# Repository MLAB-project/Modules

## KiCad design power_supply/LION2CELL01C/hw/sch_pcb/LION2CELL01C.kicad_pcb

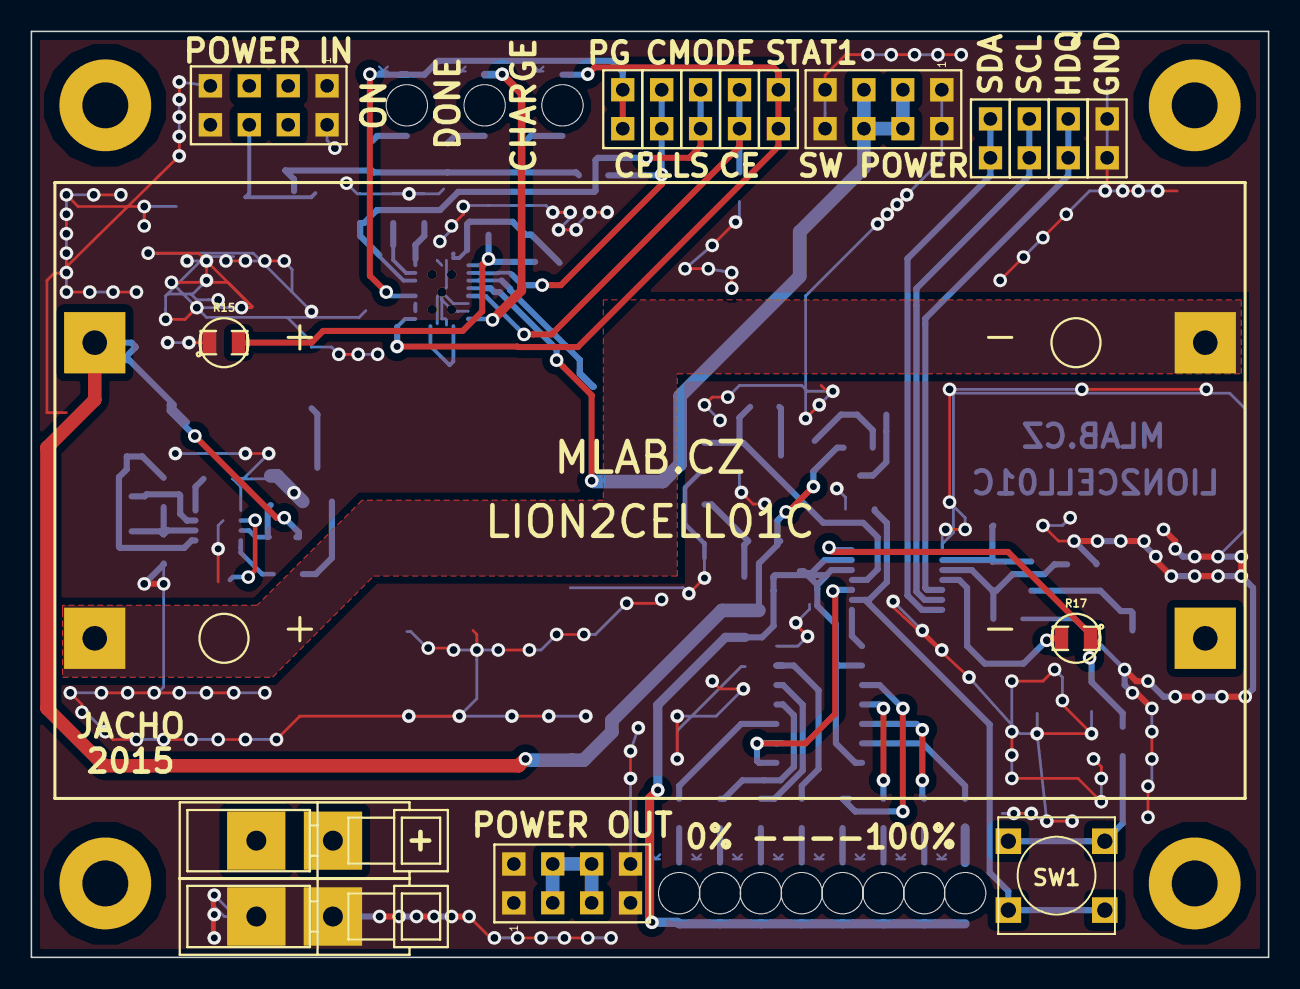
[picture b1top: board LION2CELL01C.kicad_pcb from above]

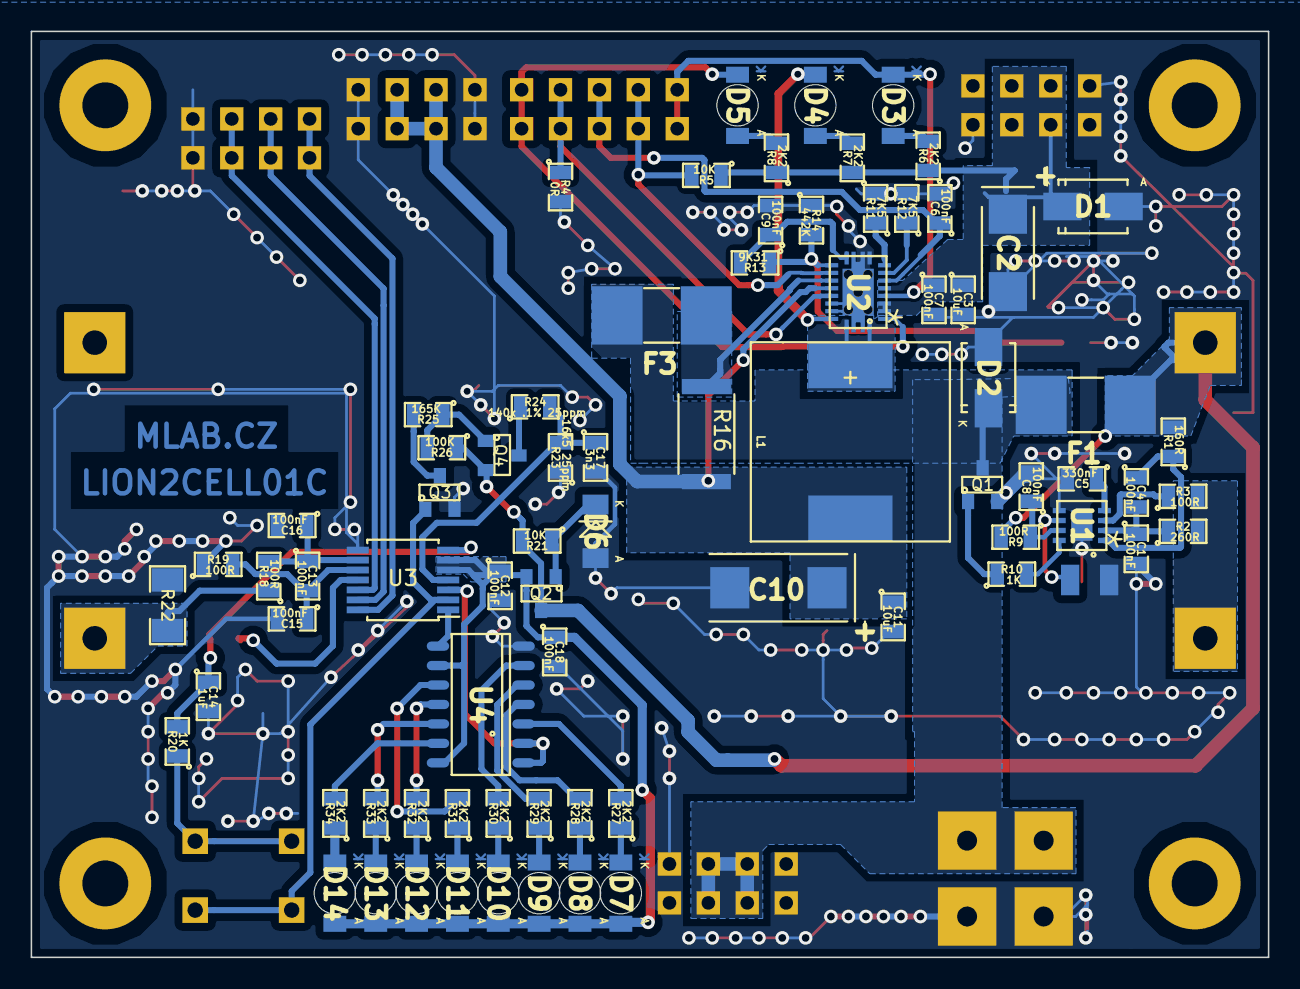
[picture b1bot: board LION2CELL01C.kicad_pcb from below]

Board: 2 copper layers, 80.8 x 60.5 mm, 98 parts (76 on the bottom side), 63 nets.

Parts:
BT1: 2x18650_LION-RESCUE-LION2CELL01C; 2LION
C1, C4, C6, C7, C8, C9, C12, C13, C15, C16, C18: 100nF; SMD-0805
C2: 47uF; TantalC_SizeC_Reflow
C3, C11: 10uF; SMD-0805
C5: 330nF; SMD-0805
C10: 100uF; TantalC_SizeD_Reflow
C14: 1uF; SMD-0805
C17: 3n3; SMD-0805
D1, D2: M4; SMA_Standard
D3, D4, D5: LED; LED_1206
D6: BZV55C-5,6V; MiniMELF_Standard
D7, D8, D9, D10, D11, D12, D13, D14: ORAGE; LED_1206
F1: 5A; Drzak_2410
F3: 2A; Drzak_2410
J1, J7, J13: JUMP_4X2; Straight_2x04
J2, J3, J4, J5, J6, J10, J11, J12, J14: JUMP_2x1; Straight_1x02
J8, J9: CONN1_1; WAGO256
J15: CONN_2; SMD_1_2x2
L1: DE1205-10
P1, P2, P3, P4: _; MountingHole_3mm
Q1: IRLML6244; SOT-23
Q2, Q3: MMBF170LT1G; SOT-23
Q4: BSS83P; SOT-23
R1: 160R; SMD-0805
R2: 260R; SMD-0805
R3, R9, R18, R19: 100R; SMD-0805
R4: 0R; SMD-0805
R5, R21: 10K; SMD-0805
R6, R7, R8, R27, R28, R29, R30, R31, R32, R33, R34: 2K2; SMD-0805
R10, R20: 1K; SMD-0805
R11, R12: 7K5; SMD-0805
R13: 9K31; SMD-0805
R14: 442K; SMD-0805
R15: NCP21XV103J03RA; SMD-0805
R16: 0R1; R_2512
R17: 10K NTC; SMD-0805
R22: 0R01 75PPM; SMD-1206
R23: 16k5 25ppm; SMD-0805
R24: 140k .1% 25ppm; SMD-0805
R25: 165K; SMD-0805
R26: 100K; SMD-0805
SW1: SW_PUSH; SW_PUSH_SMALL
U1: BQ29209; VSON-8
U2: BQ24103; VQFN-20
U3: BQ34Z100; TSSOP-14_4.4x5mm_Pitch0.65mm
U4: SN74HC164D; SO-14

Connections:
/BAT+: BT1.1, F1.1, Q2.D, Q4.S, R1.2, R9.2, R21.2, R26.1
/BAT-MIDPOINT: BT1.2, BT1.3, R2.2, R3.2
/BATTERY+: D2.2, F1.2, F3.2, J7.3, J7.4, J7.5, J7.6, J8.1, Q1.D
/BATTERY-: BT1.4, R18.1, R22.1
/CE: J5.1, J5.2, R4.1, U2.16
/CELLS: J6.1, J6.2, R5.2, U2.13
/CMODE: C6.1, J4.1, J4.2, U2.7
/HDQ: J12.1, J12.2, U3.12
/P1: U3.3, U4.1, U4.2
/P2: U3.1, U4.8
/PG: D3.2, J3.1, J3.2, U2.5
/REGIN: C12.1, C18.1, D7.1, D8.1, D9.1, D10.1, D11.1, D12.1, D13.1, D14.1, Q2.S, U3.5, U3.6, U4.9, U4.14
/SCL: J11.1, J11.2, U3.13
/SDA: J10.1, J10.2, U3.14
/STAT1: D5.2, J2.1, J2.2, U2.2
GND: C1.2, C2.2, C3.2, C5.2, C6.2, C7.2, C8.2, C9.2, C10.2, C11.2, C12.2, C14.2, C15.2, C16.2, C17.2, C18.2, D1.1, D2.1, D6.1, J1.1, J1.2, J1.7, J1.8, J7.1, J7.2, J7.7, J7.8, J9.1, J13.1, J13.2, J13.7, J13.8, J14.1, J14.2, J15.2, Q1.S, Q3.S, R4.2, R11.2, R12.2, R14.1, R15.1, R19.1, R22.2, R23.1, U1.5, U1.9, U2.10, U2.17, U2.18, U2.21, U3.8, U4.7
unnamed: C1.1, C4.2, R2.1, U1.2
unnamed: C2.1, C3.1, C7.1, D1.2, J1.3, J1.4, J1.5, J1.6, R5.1, R6.1, R7.1, R8.1, U2.3, U2.4, U2.6
unnamed: C4.1, R1.1, U1.1
unnamed: C5.1, U1.4
unnamed: C8.1, R9.1, U1.7
unnamed: C9.1, R13.2
unnamed: C10.1, C11.1, J13.3, J13.4, J13.5, J13.6, L1.2, R16.2, U2.15
unnamed: C13.1, C16.1, R18.2, U3.9
unnamed: C13.2, C15.1, R19.2, U3.10
unnamed: C14.1, R17.1, R20.2, U3.7
unnamed: C17.1, R23.2, R24.2
unnamed: D3.1, R6.2
unnamed: D4.1, R7.2
unnamed: D4.2, U2.19
unnamed: D5.1, R8.2
unnamed: D6.2, Q2.G, R21.1
unnamed: D7.2, R27.1
unnamed: D8.2, R28.1
unnamed: D9.2, R29.1
unnamed: D10.2, R30.1
unnamed: D11.2, R31.1
unnamed: D12.2, R32.1
unnamed: D13.2, R33.1
unnamed: D14.2, R34.1
unnamed: F3.1, R16.1, U2.14
unnamed: J15.1, U1.6
unnamed: L1.1, U2.1, U2.20
unnamed: Q1.G, R10.1
unnamed: Q3.D, R25.2
unnamed: Q3.G, SW1.2, U3.2
unnamed: Q4.D, R24.1
unnamed: Q4.G, R25.1, R26.2
unnamed: R3.1, U1.3
unnamed: R10.2, U1.8
unnamed: R11.1, U2.9
unnamed: R12.1, U2.8
unnamed: R13.1, R14.2, R15.2, U2.12
unnamed: R17.2, U3.11
unnamed: R20.1, SW1.1
unnamed: R27.2, U4.3
unnamed: R28.2, U4.4
unnamed: R29.2, U4.5
unnamed: R30.2, U4.6
unnamed: R31.2, U4.10
unnamed: R32.2, U4.11
unnamed: R33.2, U4.12
unnamed: R34.2, U4.13

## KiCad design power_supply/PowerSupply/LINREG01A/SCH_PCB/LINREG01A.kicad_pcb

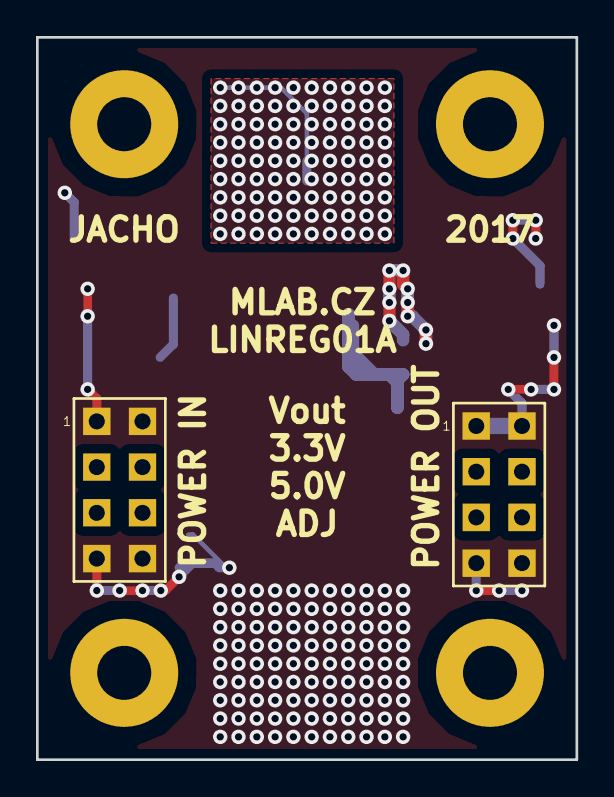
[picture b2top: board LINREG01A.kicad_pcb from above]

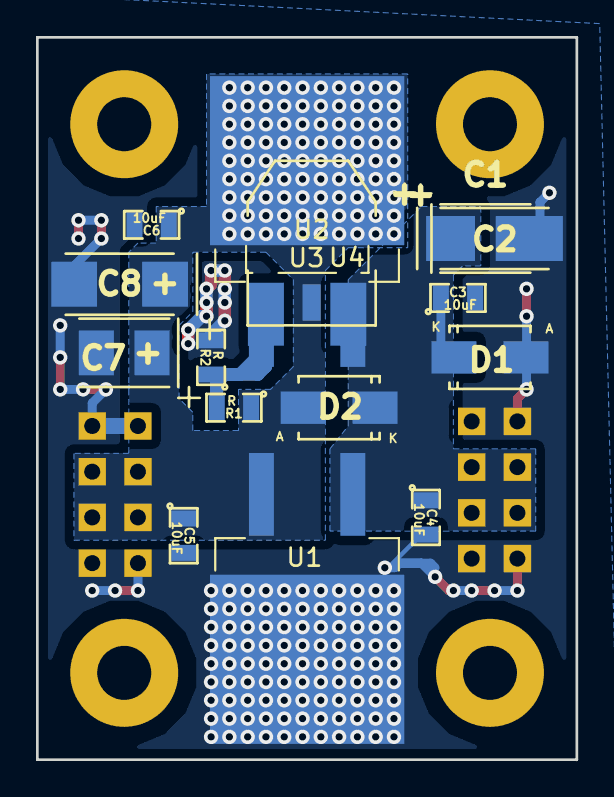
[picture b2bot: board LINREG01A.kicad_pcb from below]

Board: 2 copper layers, 30.0 x 40.1 mm, 22 parts (16 on the bottom side), 4 nets.

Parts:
C1, C7: 10uF; TantalC_SizeB_Reflow
C2, C8: 47uF; TantalC_SizeC_Reflow
C3, C4, C5, C6: 10uF; SMD-0805
D1, D2: M4; Diode-SMA_Standard
J1, J2: HEADER_2x04_PARALLEL; Straight_2x04
M1, M2, M3, M4: HOLE; MountingHole_3mm
R1, R2: R; SMD-0805
U1: L78_DPAK_D2PAK; D2PAK-TO-263-2Lead
U2: LM1117_ADJ_SOT; SOT-223
U3: LM317M_LM217_DPAK_D2PAK; D2PAK-TO-263-2Lead
U4: LM317M_LM217_DPAK_D2PAK; DPAK-TO-252-2Lead

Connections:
/ADJ: R1.2, R2.1, U2.1, U3.1, U4.1
/OUT: C5.1, C6.1, C7.1, C8.1, D2.2, J2.3, J2.4, J2.5, J2.6, R1.1, U1.3, U2.2, U2.4, U3.4, U4.4
GND: C1.2, C2.2, C3.2, C4.2, C5.2, C6.2, C7.2, C8.2, D1.2, J1.1, J1.2, J1.7, J1.8, J2.1, J2.2, J2.7, J2.8, R2.2, U1.4
VCC: C1.1, C2.1, C3.1, C4.1, D1.1, D2.1, J1.3, J1.4, J1.5, J1.6, U1.1, U2.3, U3.3, U4.3

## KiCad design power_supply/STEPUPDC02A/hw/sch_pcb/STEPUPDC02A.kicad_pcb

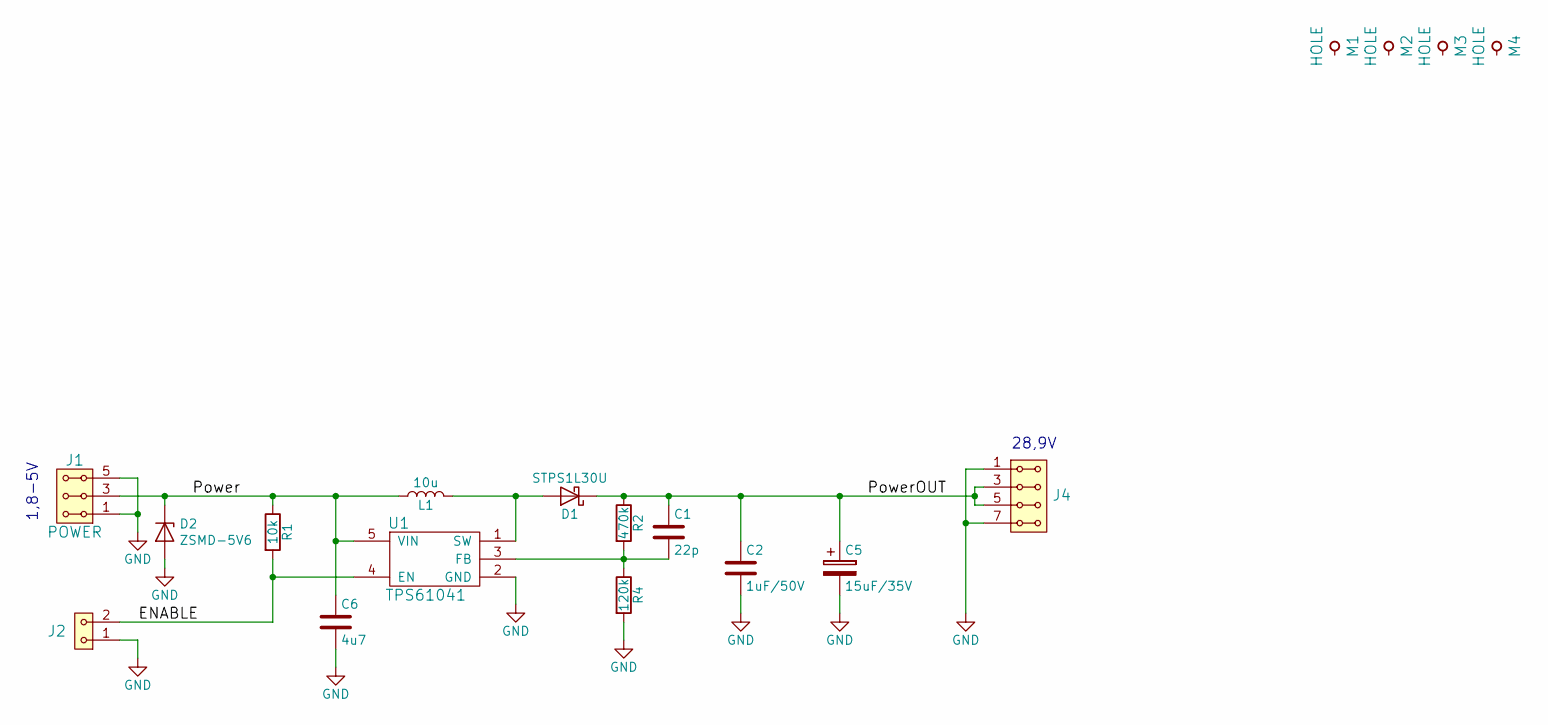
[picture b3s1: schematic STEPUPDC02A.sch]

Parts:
C1: 22p; SMD-0805
C2: 1uF/50V; SMD-0805
C5: 15uF/35V; TantalC_SizeC_Reflow
C6: 4u7; SMD-0805
D1: STPS1L30U; D_SMB
D2: ZSMD-5V6; D_MiniMELF
J1: POWER; Straight_2x03
J2: HEADER_1x02; Straight_2x01
J4: HEADER_2x04_PARALLEL; Straight_2x04
L1: 10u; DJNR5040
M1, M2, M3, M4: HOLE; MountingHole_3mm
R1: 10k; SMD-0805
R2: 470k; SMD-0805
R4: 120k; SMD-0805
U1: TPS61041; SOT-23-5_HandSoldering

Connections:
/ENABLE: J2.2, R1.2, U1.4 (EN)
/Power: C6.1, D2.1 (K), J1.3, J1.4, L1.1, R1.1, U1.5 (VIN)
/PowerOUT: C1.1, C2.1, C5.1, D1.1 (K), J4.3, J4.4, J4.5, J4.6, R2.1
GND: C2.2, C5.2, C6.2, D2.2 (A), J1.1, J1.2, J1.5, J1.6, J2.1, J4.1, J4.2, J4.7, J4.8, R4.2, U1.2 (GND)
unnamed: C1.2, R2.2, R4.1, U1.3 (FB)
unnamed: D1.2 (A), L1.2, U1.1 (SW)

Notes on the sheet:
1,8-5V
28,9V

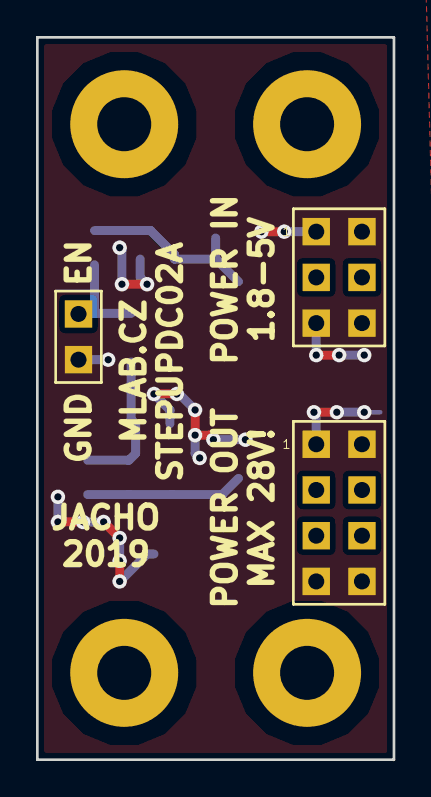
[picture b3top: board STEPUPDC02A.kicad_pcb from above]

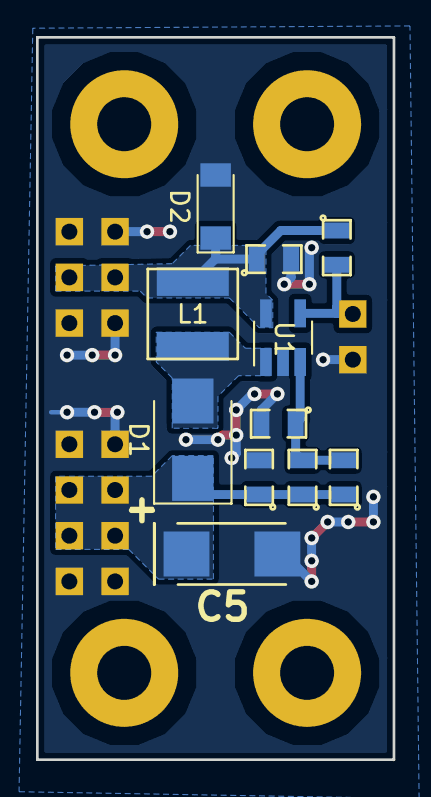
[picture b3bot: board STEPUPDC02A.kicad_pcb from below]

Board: 2 copper layers, 19.8 x 40.1 mm, 18 parts (11 on the bottom side), 6 nets.

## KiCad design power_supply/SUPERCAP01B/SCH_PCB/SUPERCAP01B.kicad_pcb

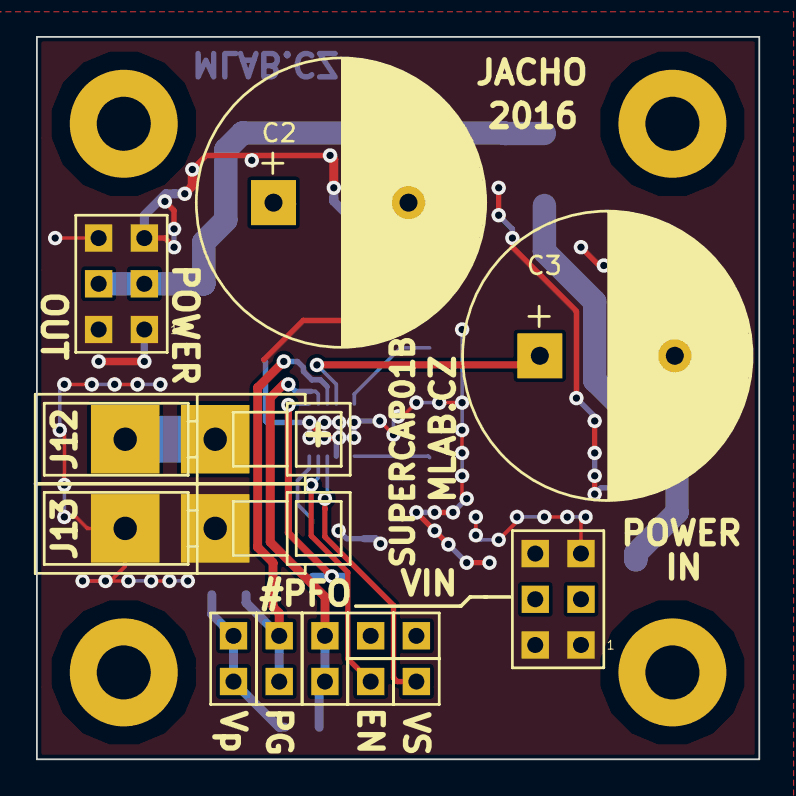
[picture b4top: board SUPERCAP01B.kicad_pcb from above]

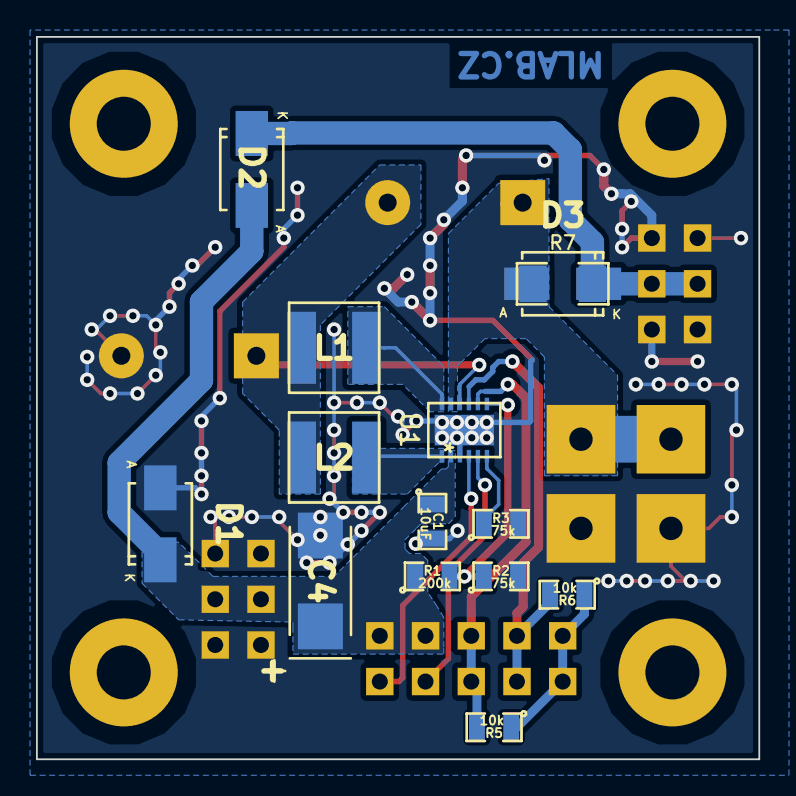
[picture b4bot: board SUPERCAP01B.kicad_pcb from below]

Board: 2 copper layers, 40.1 x 40.1 mm, 31 parts (14 on the bottom side), 14 nets.

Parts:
C1: 10uF; SMD-0805
C2, C3: 22F; C_Radial_D16_L25_P7.5
C4: 47uF; TantalC_SizeC_Reflow
D1: M4; SMA_Standard
D2, D3: 15MQ040N; Diode-SMA_Standard
J1, J11: JUMP_3X2; Straight_2x03
J5, J6, J7, J8: CONN1_1; Straight_1x01
J9, J10, J14: JUMP_2x1; Straight_2x01
J12, J13: CONN1_1; WAGO256
L1, L2: DJNR5040-3R3-S; DJNR5040
M1, M2, M3, M4: HOLE; MountingHole_3mm
R1: 200k; SMD-0805
R2, R3: 75k; SMD-0805
R5, R6: 10k; SMD-0805
R7: 0R; SMD-1206
U1: LTC3625; DFN-12-1EP_3x4mm_Pitch0.5mm

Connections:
/#PFO: J9.1, J9.2, R5.2, U1.8
/EN: J6.1, U1.5
/OUT: C2.1, D3.2, J12.1, R7.2, U1.11
/OUT2: D2.1, D3.1, J11.3, J11.4, R7.1
/PG: J10.1, J10.2, R6.2, U1.9
/VIN: C1.1, C4.1, D1.1, D2.2, J1.3, J1.4, J5.1, J7.1, R1.1, U1.2
/VSEL: J8.1, U1.4
/Vpull-up: J14.1, J14.2, R5.1, R6.1
GND: C1.2, C3.2, C4.2, D1.2, J1.1, J1.2, J1.5, J1.6, J11.1, J11.2, J11.5, J11.6, J13.1, R2.2, R3.2, U1.3, U1.13
unnamed: C2.2, C3.1, L1.2, L2.2, U1.10
unnamed: L1.1, U1.12
unnamed: L2.1, U1.1
unnamed: R1.2, R2.1, U1.7
unnamed: R3.1, U1.6

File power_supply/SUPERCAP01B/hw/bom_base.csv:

C;SMD-0805;10uF;['C1\r']
D_Schottky;Diode-SMA_Standard;15MQ040N;['D2\r', 'D3\r']
LTC3625;DFN-12-1EP_3x4mm_Pitch0.5mm;LTC3625;['U1\r']
DIODE;SMA_Standard;M4;['D1\r']
JUMP_2x1;Straight_2x01;JUMP_2x1;['J9\r', 'J10\r', 'J14\r']
CONN1_1;Straight_1x01;CONN1_1;['J7\r', 'J8\r', 'J6\r', 'J5\r']
CONN1_1;WAGO256;CONN1_1;['J12\r', 'J13\r']
R;SMD-0805;75k;['R2\r', 'R3\r']
R;SMD-0805;200k;['R1\r']
R;SMD-0805;10k;['R5\r', 'R6\r']
R;SMD-1206;0R;['R7\r']
INDUCTOR_SMALL;DJNR5040;DJNR5040-3R3-S;['L1\r', 'L2\r']
JUMP_3X2;Straight_2x03;JUMP_3X2;['J1\r', 'J11\r']
HOLE;MountingHole_3mm;HOLE;['M1\r', 'M3\r', 'M2\r', 'M4\r']
CP;TantalC_SizeC_Reflow;47uF;['C4\r']
CP;C_Radial_D16_L25_P7.5;22F;['C3\r', 'C2\r']

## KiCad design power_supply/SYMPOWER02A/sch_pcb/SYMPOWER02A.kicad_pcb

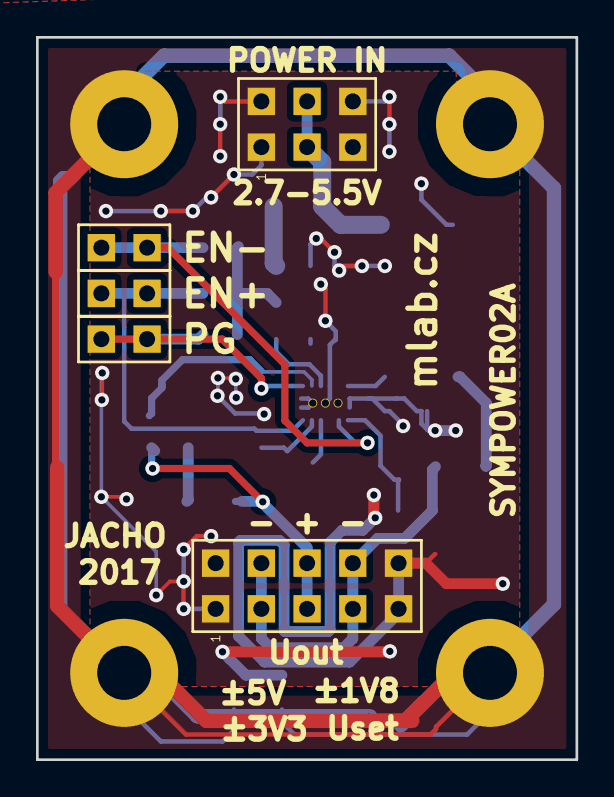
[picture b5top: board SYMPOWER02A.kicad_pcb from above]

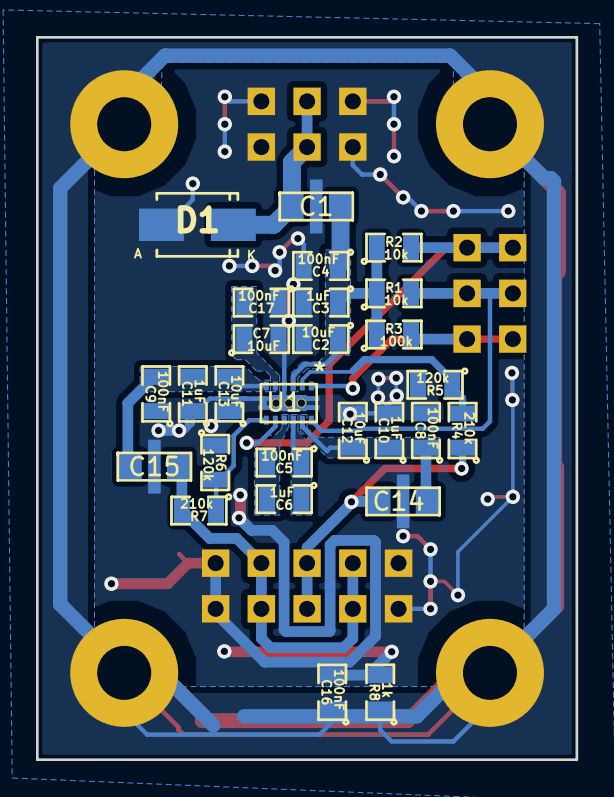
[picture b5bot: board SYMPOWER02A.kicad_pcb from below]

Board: 2 copper layers, 30.0 x 40.1 mm, 36 parts (27 on the bottom side), 16 nets.

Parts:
C1, C14, C15: NFM21PC105; FIR1
C2, C7, C12, C13: 10uF; SMD-0805
C3, C6, C10, C11: 1uF; SMD-0805
C4, C5, C8, C9, C16, C17: 100nF; SMD-0805
D1: M4; SMA_Standard
J1: HEADER_2x03_PARALLEL; Straight_2x03
J2, J3, J4: HEADER_2x01_PARALLEL; Straight_2x01
J5: HEADER_2x05_PARALLEL; Straight_2x05
M1, M2, M3, M4: HOLE; MountingHole_3mm
R1, R2: 10k; SMD-0805
R3: 100k; SMD-0805
R4, R7: 210k; SMD-0805
R5, R6: 120k; SMD-0805
R8: 1k; SMD-0805
U1: LM27762; WSON-12

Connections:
/C1+: C5.1, C6.1, U1.10
/C1-: C5.2, C6.2, U1.9
/CP: C7.1, C17.2, U1.5
/EN+: J2.1, J2.2, R1.2, U1.12
/EN-: J3.1, J3.2, R2.2, U1.8
/FB+: R4.2, R5.1, U1.2
/FB-: R6.2, R7.1, U1.7
/PGOOD: J4.1, J4.2, R3.2, U1.1
/Vout+: C14.3, J5.5, J5.6, R4.1
/Vout-: C15.3, J5.3, J5.4, J5.7, J5.8, R7.2
GND: C1.2, C2.2, C3.2, C4.2, C7.2, C8.2, C9.1, C10.2, C11.1, C12.2, C13.1, C14.2, C15.2, C16.2, C17.1, D1.2, J1.1, J1.2, J1.5, J1.6, J5.1, J5.2, J5.9, J5.10, R5.2, R6.1, R8.2, U1.4, U1.13
unnamed: C1.1, D1.1, J1.3, J1.4
unnamed: C8.1, C10.1, C12.1, C14.1, U1.11
unnamed: C9.2, C11.2, C13.2, C15.1, U1.6
unnamed: C16.1, M1.1, M2.1, M3.1, M4.1, R8.1
VCC: C1.3, C2.1, C3.1, C4.1, R1.1, R2.1, R3.1, U1.3

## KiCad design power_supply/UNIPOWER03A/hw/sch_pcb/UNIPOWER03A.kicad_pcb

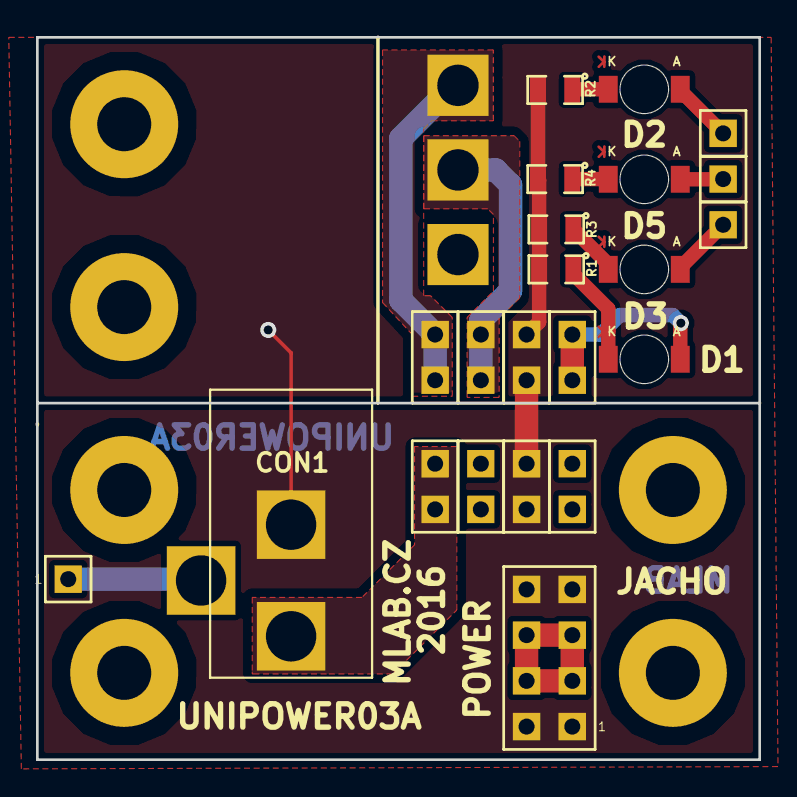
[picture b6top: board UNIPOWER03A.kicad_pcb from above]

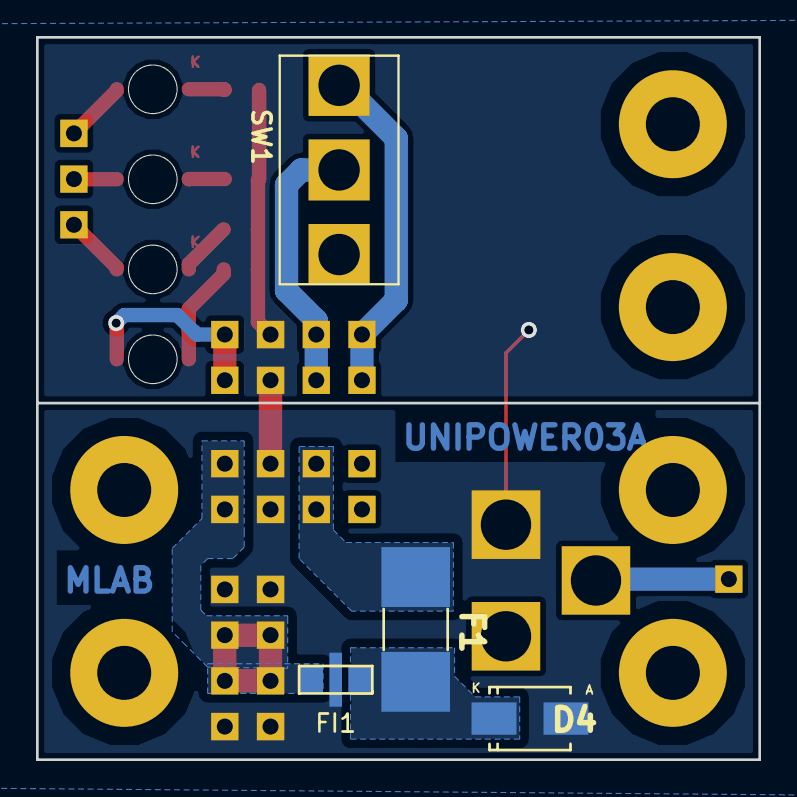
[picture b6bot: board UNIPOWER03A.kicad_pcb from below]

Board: 2 copper layers, 40.1 x 40.1 mm, 32 parts (4 on the bottom side), 16 nets.

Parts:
CON1: JACK_DC2.1; DC2,1MM
D1, D2: RED; LED_1206
D3: GREEN; LED_1206
D4: M4; Diode-SMA_Standard
D5: ORANGE; LED_1206
F1: 1,1A; Drzak_2410
FI1: NFM21PC105; FIR1
J1, J2, J4, J5: CONN1_2; Straight_1x02
J3, J9, J10, J11: JUMP_2x1; Straight_1x02
J6, J7, J12, J13: CONN1_1; Straight_1x01
J8: JUMP_4X2; Straight_2x04
M1, M2, M3, M4, M5, M8: HOLE; MountingHole_3mm
R1, R2, R3, R4: 2k2; SMD-0805
SW1: SL19121; Prepinaci_3A_SL19121

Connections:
GND: CON1.2, D4.2, FI1.2, J8.1, J8.2, J8.7, J8.8, J10.1, J10.2, J11.1, J11.2, R1.2, R2.2, R3.2, R4.2
unnamed: CON1.1, J1.1, J1.2
unnamed: CON1.3, J13.1
unnamed: D1.1, R1.1
unnamed: D1.2, J9.1, J9.2
unnamed: D2.1, R2.1
unnamed: D2.2, J6.1
unnamed: D3.1, R3.1
unnamed: D3.2, J7.1
unnamed: D4.1, F1.2, FI1.1
unnamed: D5.1, R4.1
unnamed: D5.2, J12.1
unnamed: F1.1, J5.1, J5.2
unnamed: J2.1, J2.2, SW1.1
unnamed: J4.1, J4.2, SW1.2
VCC: FI1.3, J3.1, J3.2, J8.3, J8.4, J8.5, J8.6

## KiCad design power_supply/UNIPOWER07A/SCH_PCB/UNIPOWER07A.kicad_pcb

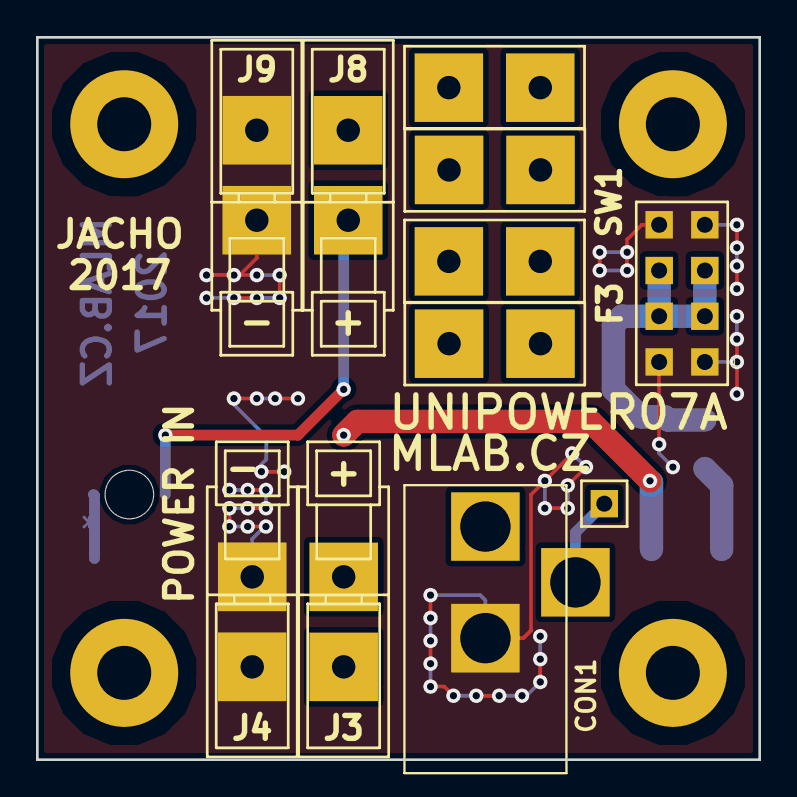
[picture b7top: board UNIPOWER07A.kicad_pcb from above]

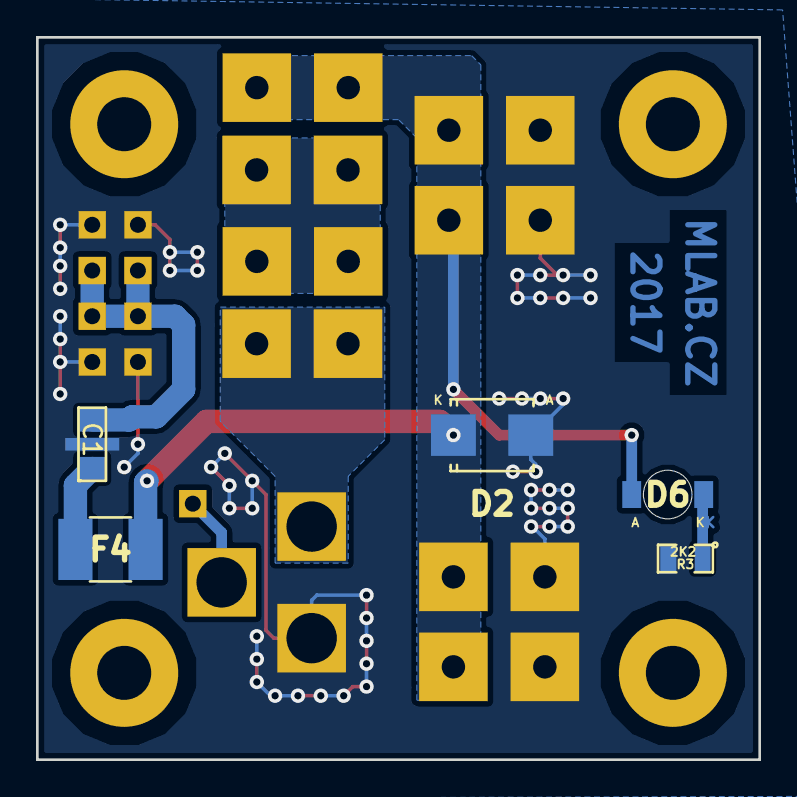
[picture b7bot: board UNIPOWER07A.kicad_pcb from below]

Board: 2 copper layers, 40.1 x 40.1 mm, 18 parts (5 on the bottom side), 8 nets.

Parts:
C1: NFM21PC105; FIR1
CON1: JACK_DC2.1; DC2,1MM
D2: SMBJ15A-E3/52; SMB_Standard
D6: RED; LED_1206
F3: 10A; 2xFaston
F4: 1.1A; 1812
J3, J4, J8, J9: CONN1_1; WAGO256
J7: CONN1_1; Straight_1x01
J12: JUMP_4X2; Straight_2x04
P1, P2, P3, P4: _; MountingHole_3mm
R3: 2K2; SMD-0805
SW1: Prepinac; 2xFaston

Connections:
GND: C1.2, CON1.2, D2.2, J4.1, J9.1, J12.1, J12.2, J12.7, J12.8, R3.2
unnamed: C1.1, F4.1
unnamed: C1.3, J12.3, J12.4, J12.5, J12.6
unnamed: CON1.1, F3.2
unnamed: CON1.3, J7.1
unnamed: D2.1, D6.2, F4.2, J3.1, J8.1, SW1.1
unnamed: D6.1, R3.1
unnamed: F3.1, SW1.2
